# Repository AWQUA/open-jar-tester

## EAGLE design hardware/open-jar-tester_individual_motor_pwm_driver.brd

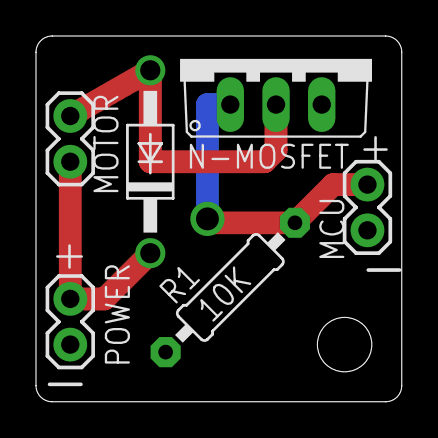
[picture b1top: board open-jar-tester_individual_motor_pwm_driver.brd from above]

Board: 2 copper layers, 20.3 x 20.3 mm, 6 parts (0 on the bottom side), 4 nets.

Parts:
D1: 1N4004; DO41-10
MCU: 1X02
MOTOR: 1X02
N-MOSFET: TO220V
POWER: 1X02
R1: 10K; 0207/10

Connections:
GND: MCU.2, N-MOSFET.3, POWER.1, R1.1
unnamed: MCU.1, N-MOSFET.1, R1.2
unnamed: D1.A, MOTOR.2, N-MOSFET.2
unnamed: D1.C, MOTOR.1, POWER.2

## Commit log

2016-08-12 added basic pwm driver board
2016-08-12 shuffling files into folders
2017-01-15 deleting temp files
2017-12-22 Create LICENSE

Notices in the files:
parts and their libraries:
SparkFun-Connectors: Licensing: Creative Commons ShareAlike 4.0 International - https://creativecommons.org/licenses/by-sa/4.0
